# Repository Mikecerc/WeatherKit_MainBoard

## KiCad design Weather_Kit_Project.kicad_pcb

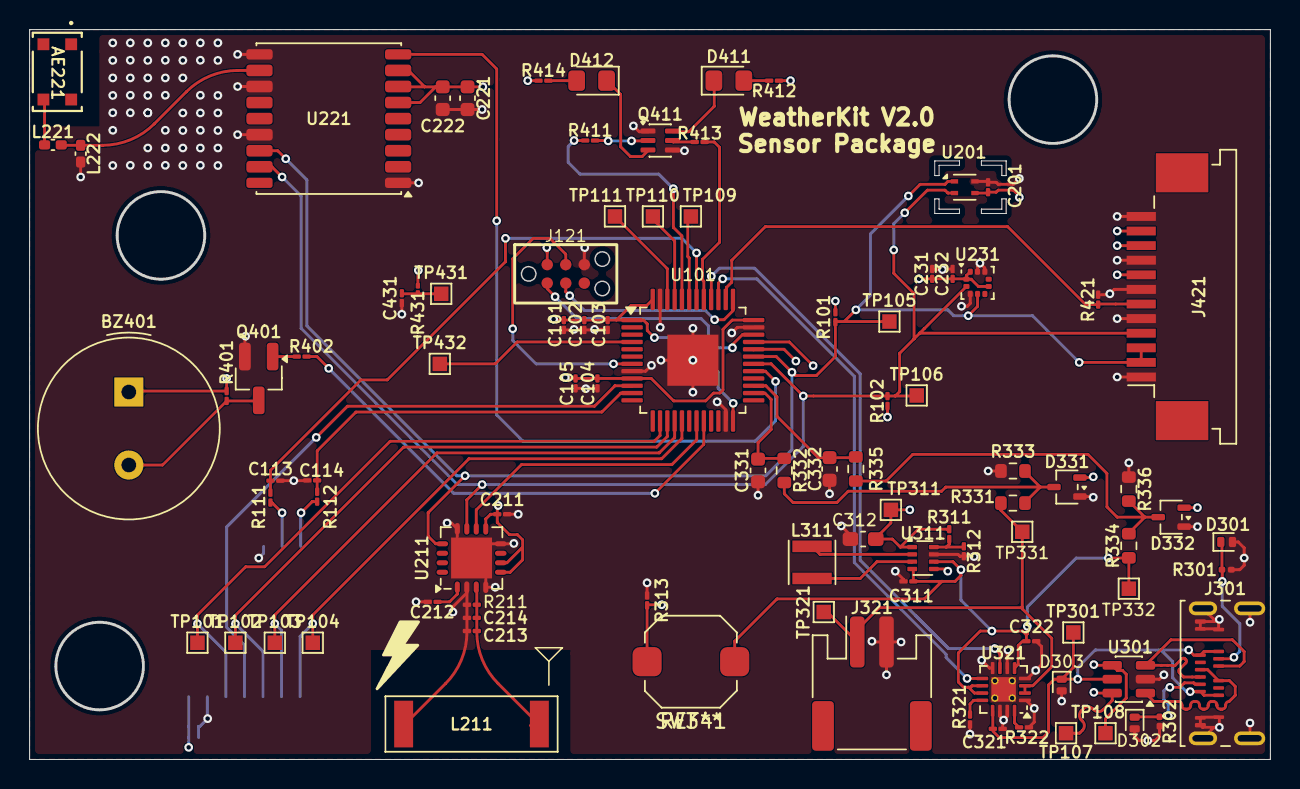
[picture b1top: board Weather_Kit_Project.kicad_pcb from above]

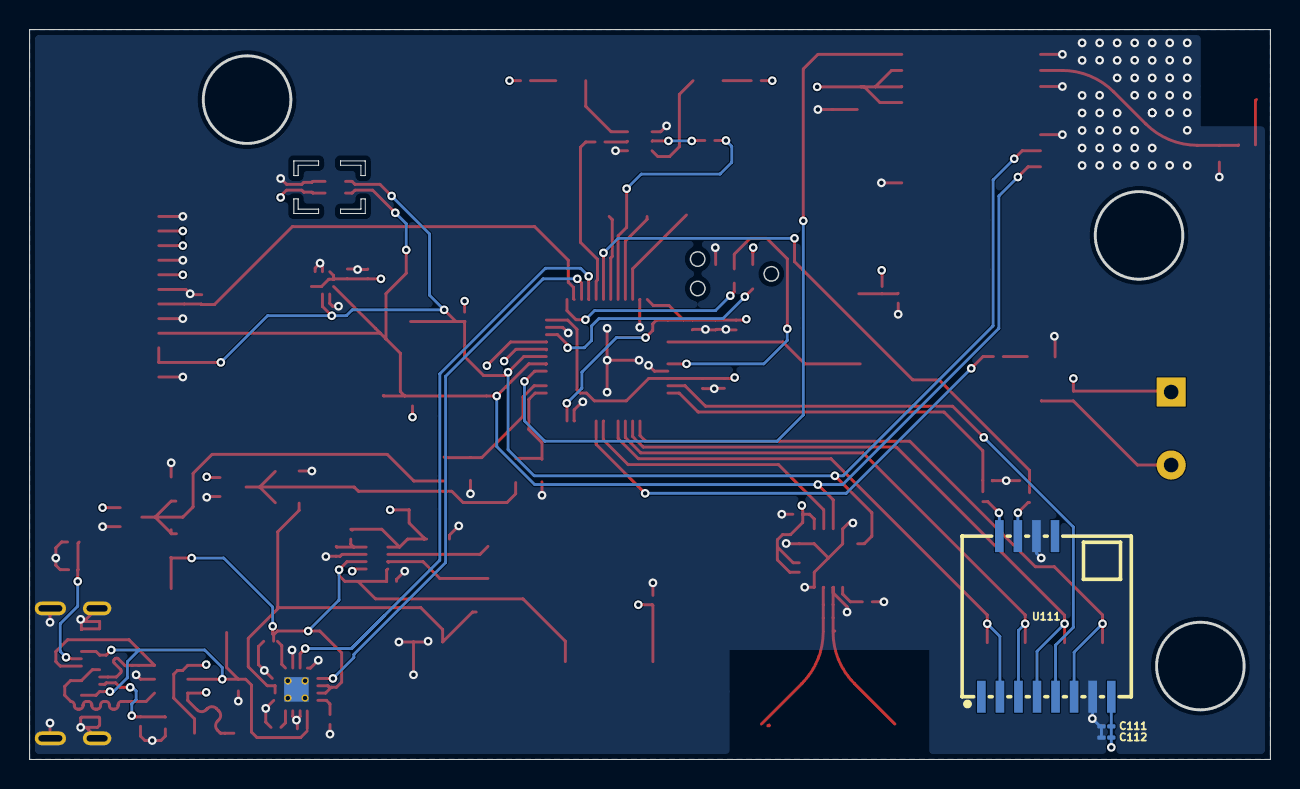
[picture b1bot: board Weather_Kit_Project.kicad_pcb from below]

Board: 4 copper layers, 85.0 x 50.0 mm, 98 parts (3 on the bottom side), 60 nets.

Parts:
AE221: 1462350001; ANT_1462350001_MOL
BZ401: Buzzer; Buzzer_TDK_PS1240P02BT_D12.2mm_H6.5mm
C101, C104, C212: 10µ; C_01005_0402Metric_Pad0.57x0.30mm_HandSolder
C102, C103, C105, C113, C114: 10n; C_01005_0402Metric_Pad0.57x0.30mm_HandSolder
C111, C201, C211, C231, C232, C431: 100n; C_01005_0402Metric_Pad0.57x0.30mm_HandSolder
C112, C321: 1µ; C_01005_0402Metric_Pad0.57x0.30mm_HandSolder
C213, C214: 470p; C_01005_0402Metric_Pad0.57x0.30mm_HandSolder
C221, C331, C332: 100n; C_0603_1608Metric
C222: 1µ; C_0603_1608Metric
C311: 22µ; C_01005_0402Metric_Pad0.57x0.30mm_HandSolder
C312: 47µ; C_0603_1608Metric_Pad1.08x0.95mm_HandSolder
C322: 4.7µ; C_01005_0402Metric_Pad0.57x0.30mm_HandSolder
D301, D302, D303: PESD5V0L1ULD; D_SOD-882D
D331, D332: BAT54SW; SOT-323_SC-70
D411: G_LED; LED_0805_2012Metric_Pad1.15x1.40mm_HandSolder
D412: R_LED; LED_0805_2012Metric_Pad1.15x1.40mm_HandSolder
J121: TC2030-IDC-NL-10; TC2030-IDC-NL
J301: USB_C_Receptacle; USB_C_Receptacle_Amphenol_124019772112A
J321: Conn_01x02; JST_PH_S2B-PH-SM4-TB_1x02-1MP_P2.00mm_Horizontal
J421: CFAL12832C0-091B-W; TE_1-84952-2_1x12-1MP_P1.0mm_Horizontal
L211: 100u; Coilcraft_MA5532-AE_RFID
L221: 5.1n; L_0402_1005Metric_Pad0.77x0.64mm_HandSolder
L222: 1.8n; L_0402_1005Metric_Pad0.77x0.64mm_HandSolder
L311: NR3015T1R5N; L_Taiyo-Yuden_NR-30xx
Q401: Q_NMOS_GSD; SOT-23_Handsoldering
Q411: Q_Dual_NMOS_S1G1D2S2G2D1; SOT-363_SC-70-6
R101, R102, R421: 4.7k; R_01005_0402Metric_Pad0.57x0.30mm_HandSolder
R111, R112, R401, R402: 1k; R_01005_0402Metric_Pad0.57x0.30mm_HandSolder
R211, R313: 10k; R_01005_0402Metric_Pad0.57x0.30mm_HandSolder
R301, R302: 5.1k; R_0201_0603Metric
R311: 511k; R_01005_0402Metric_Pad0.57x0.30mm_HandSolder
R312: 91k; R_01005_0402Metric_Pad0.57x0.30mm_HandSolder
R321: 3k; R_01005_0402Metric_Pad0.57x0.30mm_HandSolder
R322: 4.3k; R_01005_0402Metric_Pad0.57x0.30mm_HandSolder
R331, R332, R333, R334, R335, R336: 1k; R_0603_1608Metric
R411, R413: 2.2k; R_01005_0402Metric_Pad0.57x0.30mm_HandSolder
R412, R414: 300; R_01005_0402Metric_Pad0.57x0.30mm_HandSolder
R431: 10k; R_01005_0402Metric
SW341: SW_SPST; SW_Push_1TS009xxxx-xxxx-xxxx_6x6x5mm
TP101, TP102, TP103, TP104, TP105, TP106, TP107, TP108, TP109, TP110, TP111, TP301, TP311, TP321, TP331, TP332, TP431, TP432: TestPoint; TestPoint_Pad_1.0x1.0mm
U101: STM32U073C8Ux; TQFP-48-1EP_7x7mm_P0.5mm_EP3.5x3.5mm
U111: Wio-SX1262; COMM-SMD_12P-L11.6-W11.0-P1.27_114993390
U201: SHT4x; Sensirion_DFN-4_1.5x1.5mm_P0.8mm_SHT4x_NoCentralPad
U211: AS3935; MLPQ-16-1EP_4x4mm_P0.65mm_EP2.8x2.8mm
U221: MAX-M10S; ublox_MAX
U231: LPS22HHQTR; ST_HLGA-10_2x2mm_P0.5mm_LayoutBorder3x2y
U301: USBLC6-2SC6; SOT-23-6
U311: TPS631000; SOT-583-8
U321: BQ24230RGTR; VQFN-16-1EP_3x3mm_P0.5mm_EP1.68x1.68mm_ThermalVias

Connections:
+3.3V: BZ401.1 (+), C101.2, C102.2, C103.2, C104.2, C105.2, C111.1, C112.1, C201.1, C211.1, C221.1, C222.1, C231.1, C232.1, C312.2, D331.2 (K), D332.2 (K), J121.1 (VREF), J421.8, J421.10, J421.11, R101.2, R102.2, R311.2, R401.1, R412.1, R414.1, R431.2, TP311.1 (1_1), U101.1 (VBAT), U101.9 (VDDA), U101.24 (VDD), U101.36 (VDDUSB), U101.48 (VDD), U111.8 (VCC), U201.3 (VDD), U211.5 (Vdd), U211.6 (VReg), U211.9 (SI), U221.6 (V_BCKP), U221.7 (VCC_IO), U221.8 (VCC), U231.1 (Vdd_IO), U231.6 (~CS), U231.10 (VDD), U311.1 (VOUT)
/Power Network/USB_D_+: J301.A6 (D+), J301.B6 (D+), U301.3 (I/O2)
/Power Network/USB_D_-: J301.A7 (D-), J301.B7 (D-), U301.1 (I/O1)
CHRGR_PWR_OUT: C311.1, C322.1, R334.2, SW341.1 (A), TP332.1 (1_1), U311.4 (VIN), U311.6 (MODE), U321.5 (EN2), U321.10 (OUT), U321.11 (OUT)
GND: C101.1, C102.1, C103.1, C104.1, C105.1, C111.2, C112.2, C113.2, C114.2, C201.2, C211.2, C212.1, C213.1, C214.1, C221.2, C222.2, C231.2, C232.2, C311.2, C312.1, C321.2, C322.2, C331.2, C332.2, C431.1, D301.2 (A), D302.2 (A), D303.2 (A), D331.1 (A), D332.1 (A), J121.5 (GND), J301.A1 (GND), J301.A12 (GND), J301.B1 (GND), J301.B12 (GND), J301.SH (SHIELD), J321.2, J421.1, J421.5, J421.7, J421.9, J421.12, L211.1, L222.2, Q401.2 (S), Q411.1 (S), Q411.4 (S), R211.1, R301.2, R302.2, R312.1, R313.1, R321.1, R322.2, R333.1, R336.1, R421.2, U101.8 (VSSA), U101.23 (VSS), U101.35 (VSS), U101.47 (VSS), U101.49 (VSS), U111.7 (GND), U111.10 (GND), U201.4 (VSS), U211.2 (IN-), U211.4 (GND), U211.8 (CS), U211.12 (MISO), U211.17 (GNDPAD), U221.1 (GND), U221.10 (GND), U221.12 (GND), U221.15 (VIO_SEL), U231.3 (GND), U231.8 (GND), U231.9 (GND), U301.2 (GND), U311.7 (GND), U321.1 (TS), U321.4 (CE), U321.6 (EN1), U321.8 (VSS), U321.14 (TMR), U321.15 (TD), U321.17 (VSS)
I2C_CLK: J421.4, R102.1, TP106.1 (1_1), U101.30 (PA9), U201.2 (SCL), U211.11 (SCL), U221.17 (SCL), U231.2 (SCL)
I2C_DATA: J421.2, J421.3, R101.1, TP105.1 (1_1), U101.31 (PA10), U201.1 (SDA), U211.13 (MOSI/SDA), U221.16 (SDA), U231.4 (SDA)
MCU_AI_BATTERY_V: C331.1, R332.2, U101.26 (PB13)
MCU_AI_VOUT: C332.1, R335.2, U101.27 (PB14)
MCU_DI_CHRGR_CHG: U101.39 (PB3), U321.9 (CHG)
MCU_DI_CHRGR_PGOOD: U101.40 (PB4), U321.7 (PGOOD)
MCU_DI_JTAG_SWCLK: J121.4 (SWCLK), U101.37 (PA14)
MCU_DI_JTAG_SWDIO: J121.2 (SWDIO), U101.34 (PA13)
MCU_DI_JTAG_nRST: J121.3 (nRESET), U101.7 (PF2)
MCU_DI_LORA_BUSY: C113.1, R111.2, U101.42 (PB6)
MCU_DI_LORA_DIO1: C114.1, R112.2, U101.11 (PA1)
MCU_DI_LTNG_IRQ: U101.19 (PB1), U211.10 (IRQ)
MCU_DI_NAVBTN: TP432.1 (1_1), U101.4 (PC15)
MCU_DO_BZR_EN: R402.1, U101.20 (PB2)
MCU_DO_GLED: R411.2, U101.44 (PF3)
MCU_DO_GPS_RST: U101.29 (PA8), U221.9 (~RESET)
MCU_DO_LORA_RST: U101.10 (PA0), U111.5 (~NRST)
MCU_DO_OLED_RST: J421.6, R421.1, U101.38 (PA15)
MCU_DO_RLED: R413.2, U101.41 (PB5)
unnamed: AE221.3 (3_3), L221.2
unnamed: BZ401.2 (-), Q401.3 (D), R401.2
unnamed: C431.2, R431.1, TP431.1 (1_1)
unnamed: D301.1 (K), J301.B5 (CC2), R301.1
unnamed: D302.1 (K), J301.A5 (CC1), R302.1
unnamed: D331.3 (COM), R331.1, R332.1, R333.2
unnamed: D332.3 (COM), R334.1, R335.1, R336.2
unnamed: D411.2 (A), R412.2
unnamed: D411.1 (K), Q411.6 (D)
unnamed: D412.2 (A), R414.2
unnamed: D412.1 (K), Q411.3 (D)
unnamed: Q401.1 (G), R402.2
unnamed: Q411.2 (G), R411.1
unnamed: Q411.5 (G), R413.1
unnamed: R313.2, SW341.2 (B), U311.5 (EN)
unnamed: TP109.1 (1_1), U101.43 (PB7)
unnamed: TP110.1 (1_1), U101.45 (PB8)
unnamed: TP111.1 (1_1), U101.46 (PB9)
unnamed: R111.1, U111.11 (BUSY)
unnamed: R112.1, U111.12 (DIO1)
unnamed: C212.2, U211.1 (ACG)
unnamed: C213.2, C214.2, L211.2, R211.2, U211.3 (IN+)
unnamed: L221.1, L222.1, U221.11 (RF_IN)
unnamed: R311.1, R312.2, U311.8 (FB)
unnamed: L311.1, U311.3 (LX1)
unnamed: L311.2, U311.2 (LX2)
unnamed: R321.2, U321.12 (ILIM)
unnamed: R322.1, U321.16 (ISET)
SPI_CLK: TP102.1 (1_1), U101.15 (PA5), U111.4 (SCK)
SPI_MISO: TP104.1 (1_1), U101.17 (PA7), U111.2 (MISO)
SPI_MOSI: TP103.1 (1_1), U101.16 (PA6), U111.3 (MOSI)
SPI_NSS: TP101.1 (1_1), U101.14 (PA4), U111.6 (~NSS)
USB_D_N: TP107.1 (1_1), U101.32 (PA11), U301.6 (I/O1)
USB_D_P: TP108.1 (1_1), U101.33 (PA12), U301.4 (I/O2)
VBATT: J321.1, R331.2, TP321.1 (1_1), TP331.1 (1_1), U321.2 (BAT), U321.3 (BAT)
VBUS: C321.1, D303.1 (K), J301.A4 (VBUS), J301.A9 (VBUS), J301.B4 (VBUS), J301.B9 (VBUS), TP301.1 (1_1), U301.5 (VBUS), U321.13 (IN)

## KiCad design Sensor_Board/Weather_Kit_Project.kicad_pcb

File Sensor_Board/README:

This folder will contain all .sch & .pcb Files that pertain to the Sensor Board Module of Weather Kit

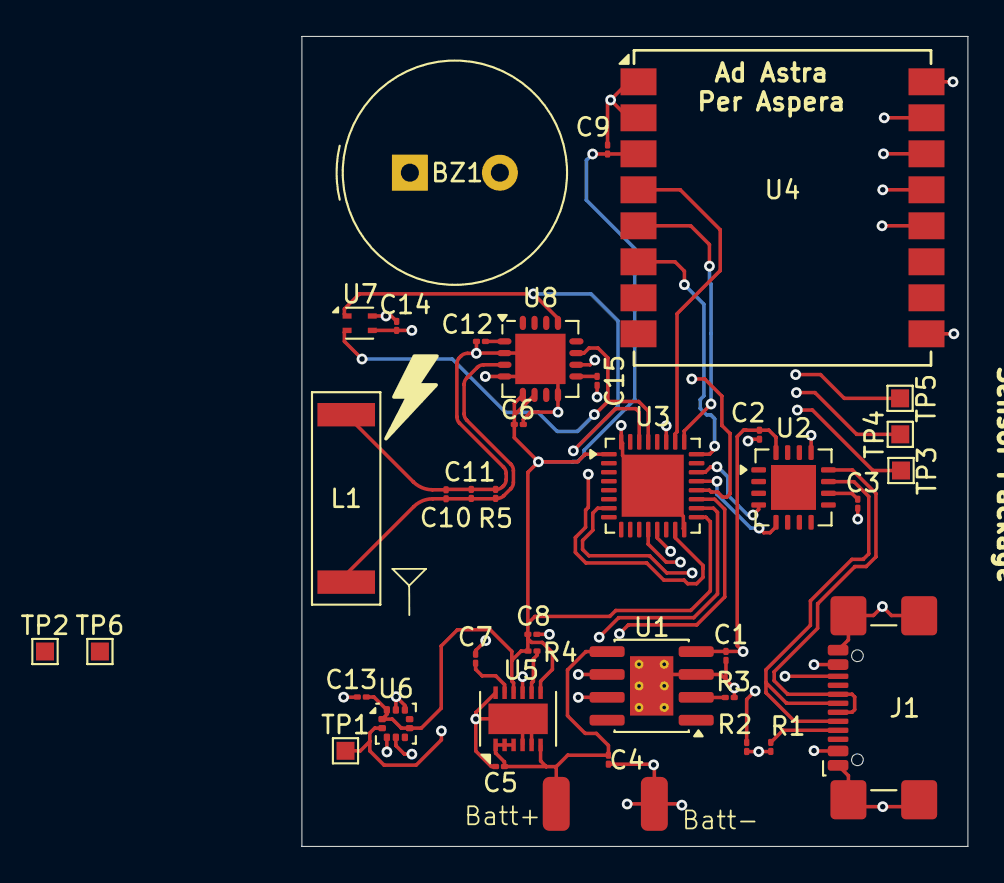
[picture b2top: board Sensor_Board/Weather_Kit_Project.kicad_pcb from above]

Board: 4 copper layers, 37.0 x 45.0 mm, 37 parts (0 on the bottom side), 31 nets.

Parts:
BZ1: Buzzer; Buzzer_TDK_PS1240P02BT_D12.2mm_H6.5mm
C1, C2, C3, C4, C8, C12: 10µF; C_01005_0402Metric
C5, C6, C7, C9, C13, C14, C15: 1µF; C_01005_0402Metric
C10, C11: 470pF; C_01005_0402Metric
J1: USB_C_Receptacle; USB_C_Receptacle_GCT_USB4110
L1: L; Coilcraft_MA5532-AE_RFID
R1, R2: 5.1kΩ; R_01005_0402Metric
R3: R; R_01005_0402Metric
R4: 500KΩ; R_01005_0402Metric
R5: 10KΩ; R_01005_0402Metric
TP1, TP2, TP3, TP4, TP5, TP6: TestPoint; TestPoint_Pad_1.0x1.0mm
U1: TP4056-42-ESOP8; SOIC-8-1EP_3.9x4.9mm_P1.27mm_EP2.41x3.3mm_ThermalVias
U2: MCP2221AxML; QFN-16-1EP_4x4mm_P0.65mm_EP2.5x2.5mm
U3: STM32U031K8Ux; QFN-32-1EP_5x5mm_P0.5mm_EP3.45x3.45mm
U4: Ai-Thinker-Ra-02; Ai-Thinker-Ra-01-LoRa
U5: LTC3245xDE; DFN-12-1EP_3x4mm_P0.5mm_EP1.7x3.3mm
U6: LPS22HH; ST_HLGA-10_2x2mm_P0.5mm_LayoutBorder3x2y
U7: SHT4x; Sensirion_DFN-4_1.5x1.5mm_P0.8mm_SHT4x_NoCentralPad
U8: AS3935; MLPQ-16-1EP_4x4mm_P0.65mm_EP2.8x2.8mm

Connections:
/3V3: C6.1, C8.2, C9.1, C13.1, C14.1, R4.1, U3.1 (VDD), U3.17 (VDD), U4.3 (VDD), U5.7 (OUTS/ADJ), U5.10 (VOUT), U6.1 (Vdd_IO), U6.6 (~CS), U6.10 (VDD), U7.3 (VDD), U8.5 (Vdd), U8.6 (VReg)
/I2C Clock: TP1.1 (1_1), U3.29 (PB6), U6.2 (SCL), U7.2 (SCL), U8.11 (SCL)
/I2C Data: TP2.1 (1_1), U3.30 (PB7), U6.4 (SDA), U7.1 (SDA), U8.13 (MOSI/SDA)
/IRQ: U3.15 (PB1), U8.10 (IRQ)
/SPI MI: TP4.1 (1_1), U3.12 (PA6), U4.13 (MISO)
/SPI MO: TP5.1 (1_1), U3.13 (PA7), U4.14 (MOSI)
/SPI SCK: TP3.1 (1_1), U3.7 (PA1), U4.12 (SCK)
/VBUS: C1.1, C2.1, J1.A4 (VBUS), J1.A9 (VBUS), J1.B4 (VBUS), J1.B9 (VBUS), U1.4 (V_{CC}), U2.16 (VDD)
GND: BZ1.2 (-), C1.2, C2.2, C3.2, C4.2, C5.1, C6.2, C8.1, C9.2, C10.1, C11.1, C12.1, C13.2, C14.2, C15.2, J1.A1 (GND), J1.A12 (GND), J1.B1 (GND), J1.B12 (GND), J1.SH (SHIELD), L1.1, R1.2, R2.2, R3.2, R5.1, U1.3 (GND), U1.9 (EPAD), U2.13 (VSS), U3.16 (VSS), U3.32 (VSS), U3.33 (VSS), U4.1 (GND), U4.2 (GND), U4.9 (GND), U4.16 (GND), U5.4 (~BURST), U5.5 (SEL1), U5.12 (GND), U5.13 (EP), U6.3 (GND), U6.8 (GND), U6.9 (GND), U7.4 (VSS), U8.2 (IN-), U8.4 (GND), U8.8 (CS), U8.17 (GNDPAD)
unnamed: C4.1, C5.2, TP6.1 (1_1), U1.5 (BAT), U5.1 (VIN), U5.2 (VIN), U5.3 (VIN), U5.6 (SEL2)
unnamed: BZ1.1 (+), U3.20 (PA10)
unnamed: J1.A5 (CC1), R1.1
unnamed: J1.B5 (CC2), R2.1
unnamed: R3.1, U1.2 (PROG)
unnamed: U1.7 (~CHRG), U3.19 (PA9)
unnamed: U1.6 (~STDBY), U3.18 (PA8)
unnamed: J1.A6 (D+), J1.B6 (D+), U2.12 (D+)
unnamed: J1.A7 (D-), J1.B7 (D-), U2.11 (D-)
unnamed: U2.4 (URx), U3.22 (PA12)
unnamed: U2.5 (UTx), U3.21 (PA11)
unnamed: C3.1, U2.10 (VUSB)
unnamed: U3.24 (PA14), U4.6 (DIO1)
unnamed: U3.25 (PA15), U4.5 (DIO0)
unnamed: U3.26 (PB3), U4.4 (~RESET)
unnamed: U3.27 (PB4), U4.15 (~NSS)
unnamed: C7.1, U5.9 (C+)
unnamed: C7.2, U5.11 (C-)
unnamed: R4.2, U5.8 (PGOOD)
unnamed: C12.2, U8.1 (ACG)
unnamed: C10.2, C11.2, L1.2, R5.2, U8.3 (IN+)
unnamed: C15.1, U8.9 (SI)
